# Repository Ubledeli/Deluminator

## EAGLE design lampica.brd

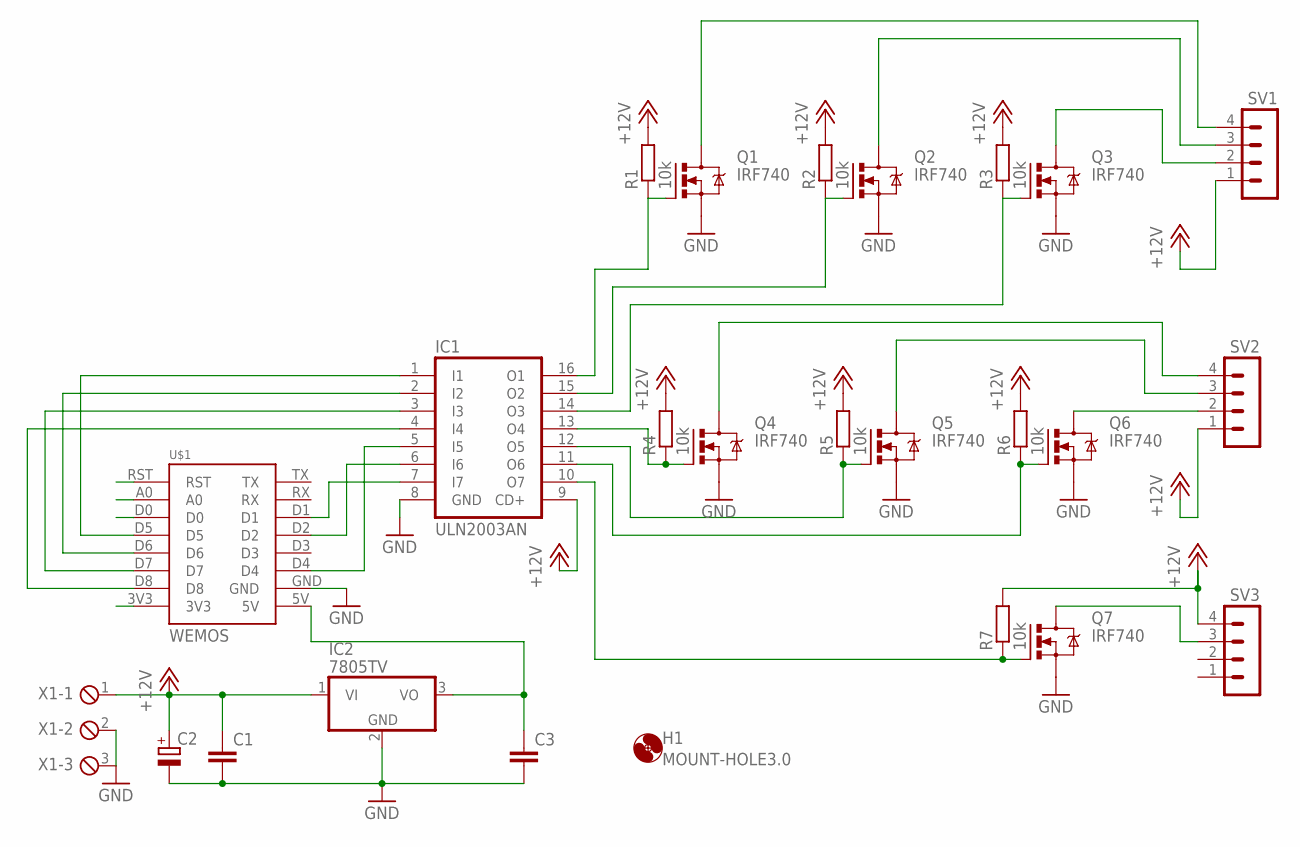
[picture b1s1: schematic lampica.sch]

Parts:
C1, C3: C-EU050-025X075; C050-025X075
C2: CPOL-EUE5-8.5; E5-8,5
H1: MOUNT-HOLE3.0; 3,0
IC1: ULN2003AN; DIL16
IC2: 7805TV; TO220V
Q1, Q2, Q3, Q4, Q5, Q6, Q7: IRF740; TO220BV
R1, R2, R3, R5, R6, R7: 10k; 0207/7
R4: 10k; 0207/10
SV1, SV2, SV3: MA04-1
U$1: WEMOS
X1: MPT3; 3POL254

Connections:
+12V: C1.1, C2.+, IC1.9 (CD+), IC2.1 (VI), R1.2, R2.2, R3.2, R4.2, R5.2, R6.2, R7.2, SV1.1, SV2.1, SV3.4, X1.1
GND: C1.2, C2.-, C3.2, IC1.8 (GND), IC2.2 (GND), Q1.S, Q2.S, Q3.S, Q4.S, Q5.S, Q6.S, Q7.S, U$1.GND, X1.2, X1.3
unnamed: IC1.4 (I4), U$1.D8
unnamed: IC1.3 (I3), U$1.D7
unnamed: C3.1, IC2.3 (VO), U$1.5V
unnamed: IC1.2 (I2), U$1.D6
unnamed: IC1.1 (I1), U$1.D5
unnamed: IC1.5 (I5), U$1.D4
unnamed: IC1.6 (I6), U$1.D2
unnamed: IC1.7 (I7), U$1.D1
unnamed: IC1.11 (O6), Q6.G, R6.1
unnamed: IC1.14 (O3), Q3.G, R3.1
unnamed: IC1.12 (O5), Q5.G, R5.1
unnamed: IC1.13 (O4), Q4.G, R4.1
unnamed: Q4.D, SV2.4
unnamed: Q5.D, SV2.3
unnamed: Q6.D, SV2.2
unnamed: IC1.10 (O7), Q7.G, R7.1
unnamed: Q7.D, SV3.3
unnamed: IC1.15 (O2), Q2.G, R2.1
unnamed: IC1.16 (O1), Q1.G, R1.1
unnamed: Q1.D, SV1.4
unnamed: Q2.D, SV1.3
unnamed: Q3.D, SV1.2

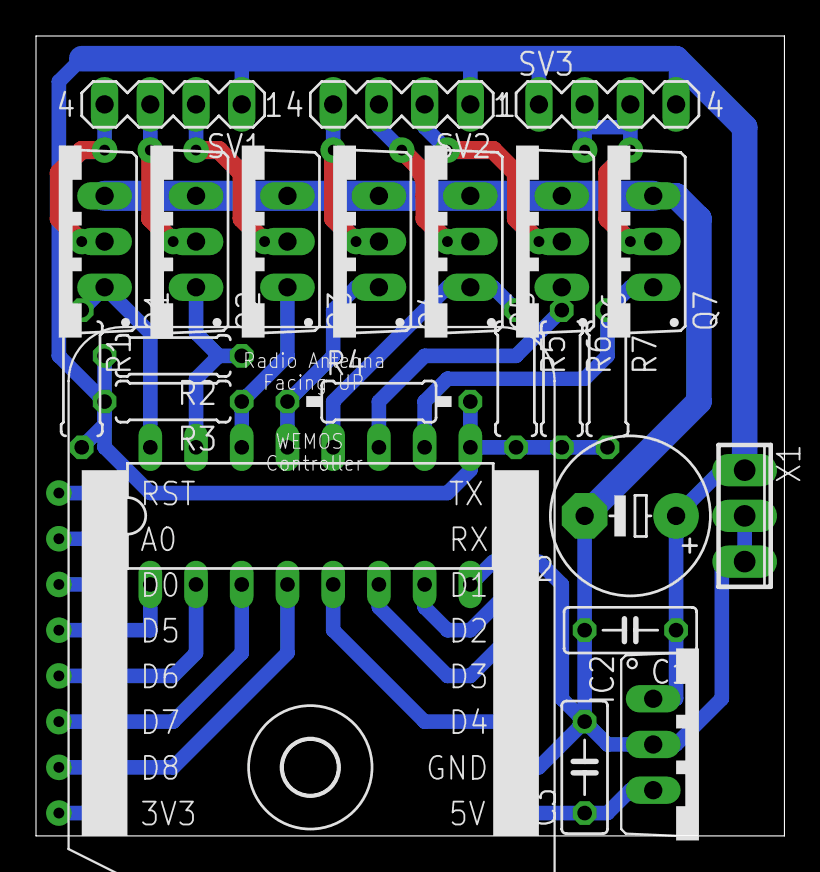
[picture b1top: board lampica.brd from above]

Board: 2 copper layers, 41.6 x 44.4 mm, 25 parts (0 on the bottom side), 24 nets.

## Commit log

2017-01-12 pictures
2017-05-12 readme
2019-11-02 micropython
